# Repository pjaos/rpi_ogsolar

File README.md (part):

# OGSolar
An off grid Solar monitoring solution. This repo defines all the hardware 
(PCB and case design) and software needed. A diagram of the system is 
shown below.

The system is sited in a shed in my garden with two 200W solar panels 
mounted on the roof of the shed. The Epsolar Tracer 4120 MPPT controller
is connected to a 40AH LION battery.

The AC OUT feed is used to power a pond pump. This is powered from the
battery when sufficient charge is available and from an AC supply when
insufficient charge is available on the battery.

The DC out feed is used to power a charging station (phones/tablets etc)
inside my house. This cuts out when the voltage on the battery drops to a
low level.

The controller is a Raspberry Pi with a PCB (detailed bellow) connected 
that provides the ability to control power, measure voltage, current 
and temperatures and also extends a WiFi network into the (metal) shed.

## Controller Hardware Design.

The OGSolar controller consists of a Raspberry Pi with a header PCB.
This header PCB provides the ability to switch two loads using MOSFET
outputs and another two loads using relay outputs. It also provides the 
ability to monitor the voltage and current drawn along with the 
temperature of the Raspberry Pi processor and the heat sink 
temperature.

The LED on the PCB will light when the unit is connected to the WiFi network.

This project is an update of a previous off grid solar project that has been running for over 7 years. Details of this project can be found [here](https://projects.pausten.me.uk/ogsolar_project.html)

## Software Design.
The software architecture chosen uses a micro services pattern. I used this project
as a testing ground for a micro services architecture. I found that 

- The initial implementation cost was a bit higher than other approaches mostly due to the
requirement to manage data flow between the entities in the system.
- Fixing bugs/issues was easier as it was generally easier to determine the root cause of
performance issues due to the nature of distributed system responsibilities. 

The above architecture uses a Tornado web server. This presents a local web interface (shown below). 
The web interface uses bootstrap to allow the layout to resize itself. 
I used [bootstrap studio](https://bootstrapstudio.io/) to design the web interface as this 
reduced the effort required to design a maintain a web interface. 
The ogsolar/www folder contains a bootstrap studio project file for the design.

The software running on the Raspberry Pi also connects to the [Yview Framework](https://github.com/pjaos/yview)
which allows integration with servers running database systems and webservers. 
The OGSolar device works without connecting to the YView network but the YView
network provides access to a wider network of devices using technologies such 
as MQTT servers. An example of the OGsolar unit providing data to such a
system can be found [here](https://projects.pausten.me.uk/ogsolar_history.html).
This shows live data from a running OGSolar unit.

### Embedded Device Software
The OGSolar device is command line driven. When the ogsolar package is installed two programs are available 'ogsolar' and 'tracer'. ogsolar is the application that runs the system operation and tracer is a command line tool that allows direct connection to the EPSolar Tracer 4210 MPPT solar charger. 

#### OGSolar
The ogsolar application can be executed from the Linux command line and has help text as shown below.

```
ogsolar -h
Usage: An application to control an off grid solar installation. Specifically for use with an EPSolar Tracer MPPT controller connected to a battery (Lithium or Lead Acid). An inverter can be used to power devices when sufficient charge is available on the battery.

Options:
  -h, --help            show this help message and exit
  --config              Set the configuration parameters.
  --cal                 Calibrate the voltage and current measurements.
  --quiet               Do not display messages on stdout.
  --inv_on              On startup set the inverter on and select the inverter
                        output. By default the inverter is off and mains AC is
                        selected.
  --web_root=WEB_ROOT   The web root dir (default=/tmp/ogsolar_webroot).
  --max_mem_inc=MAX_MEM_INC
                        The maximum memory (RAM) increase of ogsolar
                        controller software before rebooting the system
                        (default = 10000 kB).
  --sim_json=SIM_JSON   Developer use only. Simulate tracer MPPT Ctrl
                        hardware. A JSON file is needed as the argument. This
                        is a file saved using menu option 2 when running the
                        tracer command. This saves a JSON file with the state
                        of all the tracer unit registers.
  --tracer_log=TRACER_LOG
                        Log file for EPSolar Tracer register values (default =
                        none). If --sim_tracer is used then tracer register
                        values are read from this file. If --sim_tracer is not
                        used then register values read from the Tracer
                        hardware are written (appended) to this file.
  --sim_ads1115         Developer use only. Simulate the ADS1115 ADC on I2c
                        bus hardware.
  --off                 Switch off inverter and spare relay.
  --debug               Enable debugging.
  --no_reboot           In the event of an error a reboot will occur to try
                        and recover. If this option is used this does not
                        occur.
  --enable_auto_start   Auto start when this computer starts.
  --user=USER           The user name when the --enable_auto_start argument is
                        used (default=auser)
  --disable_auto_start  Disable auto starting when this computer starts.
  --check_auto_start    Check the status of an auto started ogsolar instance.
  --dv                  Debug the voltage reading. Read and display the
                        voltage every second.
  --dc                  Debug the current reading. Read and display the
                        current (Amps) every second.
  --dht                 Debug the heatsink temperature reading. Read and
                        display the temperature every second.
  --dpt                 Debug the processor temperature reading. Read and
                        display the temperature every second.
  --tgpio               Toggle the GPIO lines for debugging purposes.
  --rsw                 Read the state of the switch for debugging purposes.
  --l1=L1               Set load 1 on/off (1/0) for debugging purposes. This
                        output should be connected to the inverter.
  --l2=L2               Set load 2 on/off (1/0) for debugging purposes.
  --invr=INVR           Set the inverter relay output on/off (1/0) for
                        debugging purposes.
  --sparer=SPARER       Set the spare relay output on/off (1/0) for debugging
                        purposes.
```

Once configured as detailed [here](docs/commissioning_the_raspberry_pi.md) the solar command can be executed from the command line (without arguments) and will produce output similar to that detailed below.

```
auser@raspberrypi:/tmp $ ogsolar
INFO:  Loaded config from /home/auser/.ogsolar.cfg
INFO:  STARTUP: ogsolar
INFO:  Starting web server.INFO:  Listening on UDP port 2934
INFO:  Turn spare relay OFF
INFO:  select AC source from Mains AC
INFO:  Set inverter output OFF.
INFO:  Set inverter output OFF.
INFO:  Loaded config from /home/auser/.ogsolar_adc_cal.cfg
INFO:  Set inverter off initial state.
INFO:  Set inverter output OFF.
INFO:  Turned load 1 OFF
INFO:  select AC source from Mains AC
INFO:  ------------------> Selected AC from mains supply.
INFO:  Set inverter output ON.
INFO:  Turned load 2 ON
INFO:  Heat sink: 22.3 °C
INFO:  CPU:       40.3 °C
INFO:  Load AMPS: 0.286, Load WATTS 4.263
INFO:  Battery charge state = Not Charging
INFO:  Load 1 OFF:  Battery volts: 14.600. Waiting for battery voltage to reach 15.950 volts.
INFO:  Load 2 ON:  Battery volts: 14.600. Waiting for battery voltage to drop to 14.400 volts.
INFO:  STARTUP: 9 threads running
INFO:  9 threads running (min=8).
INFO:  Memory in use = 18772 kB, increase since startup = 0 kB (max = 10000 kB).
INFO:  Seconds since last AYT reception: 5
INFO:  ipAddress=192.168.1.93
INFO:  Listening on UDP port 2934
INFO:  Turned LED ON
INFO:  9 threads running (min=8).
INFO:  Memory in use = 18772 kB, increase since startup = 0 kB (max = 10000 kB).
INFO:  Heat sink: 22.3 °C
INFO:  CPU:       40.2 °C
INFO:  Load AMPS: 0.262, Load WATTS 3.906
INFO:  Battery charge state = Not Charging
INFO:  Load 1 OFF:  Battery volts: 14.590. Waiting for battery voltage to reach 15.950 volts.
INFO:  Load 2 ON:  Battery volts: 14.590. Waiting for battery voltage to drop to 14.400 volts.
INFO:  9 threads running (min=8).
INFO:  Memory in use = 18936 kB, increase since startup = 164 kB (max = 10000 kB).
INFO:  ipAddress=192.168.1.93
INFO:  Heat sink: 22.3 °C
INFO:  CPU:       40.1 °C
INFO:  Load AMPS: 0.273, Load WATTS 4.067
INFO:  Battery charge state = Not Charging
INFO:  Load 1 OFF:  Battery volts: 14.590. Waiting for battery voltage to reach 15.950 volts.
INFO:  Load 2 ON:  Battery volts: 14.590. Waiting for battery voltage to drop to 14.400 volts.
INFO:  9 threads running (min=8).
INFO:  Memory in use = 18936 kB, increase since startup = 164 kB (max = 10000 kB).
INFO:  ipAddress=192.168.1.93
INFO:  9 threads running (min=8).
INFO:  Memory in use = 18936 kB, increase since startup = 164 kB (max = 10000 kB).
INFO:  Heat sink: 22.3 °C
INFO:  CPU:       40.1 °C
INFO:  Load AMPS: 0.268, Load WATTS 3.994
INFO:  Battery charge state = Not Charging
INFO:  Load 1 OFF:  Battery volts: 14.600. Waiting for battery voltage to reach 15.950 volts.
INFO:  Load 2 ON:  Battery volts: 14.600. Waiting for battery voltage to drop to 14.400 volts.
INFO:  9 threads running (min=8).
INFO:  Memory in use = 18936 kB, increase since startup = 164 kB (max = 10000 kB).
```

The application will monitor the battery voltage and turn on load 1 & 2 if above a minimum voltages. Separate on/off voltage levels can be configured for Load 1 and Load 2. Other information is also reported (E.G heatsink, CPU temperature and Tracer MPPT unit register values). The OGsolar device can be configured to generate syslog data which can be sent to an external syslog server (it is not recommended that the local RPi syslog server is ued to to excessive SD card writes). An example of this data from the syslog server is shown below.

```
pja@lmserver:~$ sudo tail -f /var/log/syslog | grep 192.168.1.98
Oct 19 05:00:27 192.168.1.98 14399 root: STARTUP: ogsolar
Oct 19 05:00:30 192.168.1.98 14439 auser: STARTUP: ogsolar
Oct 19 05:00:30 192.168.1.98 14439 auser: Listening on UDP port 2934
Oct 19 05:00:30 192.168.1.98 14439 auser: Starting web server.
Oct 19 05:00:30 192.168.1.98 14439 auser: Turn spare relay OFF
Oct 19 05:00:30 192.168.1.98 14439 auser: select AC source from Mains AC
Oct 19 05:00:30 192.168.1.98 14439 auser: Set inverter output OFF.
Oct 19 05:00:30 192.168.1.98 14439 auser: Set inverter output OFF.
Oct 19 05:00:30 192.168.1.98 14439 auser: CODES_PER_AMP = 1221
Oct 19 05:00:30 192.168.1.98 14439 auser: CODES_PER_VOLT = 1270
Oct 19 05:00:30 192.168.1.98 14439 auser: NO_CURRENT_CODES = 64
Oct 19 05:00:30 192.168.1.98 14439 auser: Loaded config from /home/auser/.ogsolar_adc_cal.cfg
Oct 19 05:00:30 192.168.1.98 14439 auser: Set inverter off initial state.
Oct 19 05:00:30 192.168.1.98 14439 auser: Set inverter output OFF.
Oct 19 05:00:30 192.168.1.98 14439 auser: Turned load 1 OFF
Oct 19 05:00:32 192.168.1.98 14439 auser: select AC source from Mains AC
Oct 19 05:00:32 192.168.1.98 14439 auser: ------------------> Selected AC from mains supply.
Oct 19 05:00:32 192.168.1.98 14439 auser: Set inverter output ON.
Oct 19 05:00:32 192.168.1.98 14439 auser: Turned load 2 ON
Oct 19 05:00:32 192.168.1.98 14439 auser: EPSolarTracerInterface:_processCmd: 1
Oct 19 05:00:33 192.168.1.98 14439 auser: >>>>>>>>>>>>>>>>>>>>>>>>>>>>> Min battery charge temp (C): 0.0
Oct 19 05:00:33 192.168.1.98 14439 auser: BATTERY CHARGE STATUS=Not Charging
Oct 19 05:00:33 192.168.1.98 14439 auser: PV VOLTS=0
Oct 19 05:00:33 192.168.1.98 14439 auser: PV AMPS=0
Oct 19 05:00:33 192.168.1.98 14439 auser: BATTERY VOLTS=14.59
Oct 19 05:00:33 192.168.1.98 14439 auser: BATTERY AMPS IN=0
Oct 19 05:00:33 192.168.1.98 14439 auser: PV WATTS=0
Oct 19 05:00:33 192.168.1.98 14439 auser: BATTERY WATTS IN=0
Oct 19 05:00:33 192.168.1.98 14439 auser: BATTERY TEMPERATURE (C)=14.59
Oct 19 05:00:33 192.168.1.98 14439 auser: CONTROLLER TEMPERATURE (C)=17.8
Oct 19 05:00:33 192.168.1.98 14439 auser: MPPT_LOAD_VOLTS=0
Oct 19 05:00:33 192.168.1.98 14439 auser: MPPT_LOAD_AMPS=0
Oct 19 05:00:33 192.168.1.98 14439 auser: MPPT_LOAD_WATTS=0
Oct 19 05:00:33 192.168.1.98 14439 auser: GENERATED KW=744.1
Oct 19 05:00:33 192.168.1.98 14439 auser: GENERATED KW TODAY=0
Oct 19 05:00:33 192.168.1.98 14439 auser: GENERATED KW THIS MONTH=8.02
Oct 19 05:00:33 192.168.1.98 14439 auser: GENERATED KW THIS YEAR=63.71
Oct 19 05:00:33 192.168.1.98 14439 auser: Heat sink: 22.3 C
Oct 19 05:00:33 192.168.1.98 14439 auser: CPU:       40.1 C
Oct 19 05:00:33 192.168.1.98 14439 auser: AMPS = 0.283
Oct 19 05:00:33 192.168.1.98 14439 auser: Load AMPS: 0.283, Load WATTS 4.225
Oct 19 05:00:33 192.168.1.98 14439 auser: Battery charge state = Not Charging
Oct 19 05:00:33 192.168.1.98 14439 auser: Load 1 OFF:  Battery volts: 14.590. Waiting for battery voltage to reach 15.950 volts.
Oct 19 05:00:33 192.168.1.98 14439 auser: Load 2 ON:  Battery volts: 14.590. Waiting for battery voltage to drop to 14.400 volts.
Oct 19 05:00:35 192.168.1.98 14439 auser: STARTUP: 9 threads running
Oct 19 05:00:35 192.168.1.98 14439 auser: 9 threads running (min=8).
Oct 19 05:00:35 192.168.1.98 14439 auser: Memory in use = 18496 kB, increase since startup = 0 kB (max = 10000 kB).
Oct 19 05:00:40 192.168.1.98 14439 auser: 9 threads running (min=8).
Oct 19 05:00:40 192.168.1.98 14439 auser: Memory in use = 18892 kB, increase since startup = 396 kB (max = 10000 kB).
Oct 19 05:00:40 192.168.1.98 14439 auser: EPSolarTracerInterface:_processCmd: 1
Oct 19 05:00:41 192.168.1.98 14439 auser: >>>>>>>>>>>>>>>>>>>>>>>>>>>>> Min battery charge temp (C): 0.0
Oct 19 05:00:41 192.168.1.98 14439 auser: BATTERY CHARGE STATUS=Not Charging
Oct 19 05:00:41 192.168.1.98 14439 auser: PV VOLTS=0.02
Oct 19 05:00:41 192.168.1.98 14439 auser: PV AMPS=0
Oct 19 05:00:41 192.168.1.98 14439 auser: BATTERY VOLTS=14.59
Oct 19 05:00:41 192.168.1.98 14439 auser: BATTERY AMPS IN=0
Oct 19 05:00:41 192.168.1.98 14439 auser: PV WATTS=0
Oct 19 05:00:41 192.168.1.98 14439 auser: BATTERY WATTS IN=0
Oct 19 05:00:41 192.168.1.98 14439 auser: BATTERY TEMPERATURE (C)=14.58
Oct 19 05:00:41 192.168.1.98 14439 auser: CONTROLLER TEMPERATURE (C)=17.8
Oct 19 05:00:41 192.168.1.98 14439 auser: MPPT_LOAD_VOLTS=0
Oct 19 05:00:41 192.168.1.98 14439 auser: MPPT_LOAD_AMPS=0
Oct 19 05:00:41 192.168.1.98 14439 auser: MPPT_LOAD_WATTS=0
Oct 19 05:00:41 192.168.1.98 14439 auser: GENERATED KW=744.1
Oct 19 05:00:41 192.168.1.98 14439 auser: GENERATED KW TODAY=0
Oct 19 05:00:41 192.168.1.98 14439 auser: GENERATED KW THIS MONTH=8.02
Oct 19 05:00:41 192.168.1.98 14439 auser: GENERATED KW THIS YEAR=63.71
Oct 19 05:00:41 192.168.1.98 14439 auser: Heat sink: 22.3 C
Oct 19 05:00:41 192.168.1.98 14439 auser: CPU:       40.0 C
Oct 19 05:00:41 192.168.1.98 14439 auser: AMPS = 0.274
Oct 19 05:00:41 192.168.1.98 14439 auser: Load AMPS: 0.274, Load WATTS 4.090
Oct 19 05:00:41 192.168.1.98 14439 auser: Battery charge state = Not Charging
Oct 19 05:00:41 192.168.1.98 14439 auser: Load 1 OFF:  Battery volts: 14.590. Waiting for battery voltage to reach 15.950 volts.
Oct 19 05:00:41 192.168.1.98 14439 auser: Load 2 ON:  Battery volts: 14.590. Waiting for battery voltage to drop to 14.400 volts.
Oct 19 05:00:42 192.168.1.98 14439 auser: Seconds since last AYT reception: 5
Oct 19 05:00:42 192.168.1.98 14439 auser: Listening on UDP port 2934
Oct 19 05:00:45 192.168.1.98 14439 auser: 9 threads running (min=8).
Oct 19 05:00:45 192.168.1.98 14439 auser: Memory in use = 18904 kB, increase since startup = 408 kB (max = 10000 kB).
Oct 19 05:00:46 192.168.1.98 14439 auser: ipAddress=192.168.1.98
Oct 19 05:00:46 192.168.1.98 14439 auser: Turned LED ON
```

#### Tracer
The tracer application can be executed from the Linux command line and has help text as shown below.

```
auser@raspberrypi:/tmp $ tracer -h
usage: tracer.py [-h] [-d] [-p PORT]

Responsible for access to read and write EPSolar Tracer registers.
via the modbus interface over the RS485 serial interface.
The Raspberry PI must have a USB RS485 adaptor connected to a USB port.

optional arguments:
  -h, --help            show this help message and exit
  -d, --debug           Enable debugging.
  -p PORT, --port PORT  The USB port (default=/dev/ttyUSB0).
```

When executed from the command line the tracer command shows a menu of options as shown below. The example below shows a read of all the Tracer devices registers over the modbus interface. The interface to the EPSolar tracer unit was written as part of the OGSolar application.

```
auser@raspberrypi:/tmp $ tracer
INFO:   1: Read all registers
INFO:   2: Save registers to JSON file.
INFO:   3: Load registers from a JSON file.
INFO:   4: Save registers to JSON file.
INFO:   5: Register read.
INFO:   6: Register write.
INFO:   7: Quit
INPUT: Select a menu option: 1
INFO:  Read all registers
INFO:  Took 0.6 seconds to read all registers.
INFO:  ----------------------------------------------------------
self._address          = 0x0002/2
self._regName          = Manual control the load
self._descriptionLines = ('When the load is manual mode，1-manual on 0 -manual off',)
self._unit             = UNDEFINED
self._multiplier       = 1
self._access           = C_R/W
self._rawRegValue      = 0
self._value            = 0
self._lswRegName       = None
INFO:  ----------------------------------------------------------
self._address          = 0x0005/5
self._regName          = Enable load test mode
self._descriptionLines = ('1 Enable', '0 Disable(normal)')
self._unit             = UNDEFINED
self._multiplier       = 1
self._access           = C_R/W
self._rawRegValue      = 0
self._value            = 0
self._lswRegName       = None
INFO:  ----------------------------------------------------------
self._address          = 0x0006/6
self._regName          = Force the load on/off
self._descriptionLines = ('1 Turn on', '0 Turn off (used for temporary test of the load)')
self._unit             = UNDEFINED
self._multiplier       = 1
self._access           = C_R/W
self._rawRegValue      = 0
self._value            = 0
self._lswRegName       = None
INFO:  ----------------------------------------------------------
self._address          = 0x2000/8192
self._regName          = Over temperature inside the device
self._descriptionLines = ('1 The temperature inside the controller is higher than the over-temperature protection point.', '0 Normal')
self._unit             = UNDEFINED
self._multiplier       = 1
self._access           = D_R
self._rawRegValue      = 0
self._value            = 0
self._lswRegName       = None
INFO:  ----------------------------------------------------------
self._address          = 0x200c/8204
self._regName          = Day/Night
self._descriptionLines = ('1-Night, 0-Day',)
self._unit             = UNDEFINED
self._multiplier       = 1
self._access           = D_R
self._rawRegValue      = 1
self._value            = 1.0
self._lswRegName       = None
INFO:  ----------------------------------------------------------
self._address          = 0x3000/12288
self._regName          = Charging equipment rated input voltage
self._descriptionLines = ('PV array rated voltage',)
self._unit             = V
self._multiplier       = 100
self._access           = R
self._rawRegValue      = 10000
self._value            = 100.0
self._lswRegName       = None
INFO:  ----------------------------------------------------------
self._address          = 0x3001/12289
self._regName          = Charging equipment rated input current
self._descriptionLines = ('PV array rated current',)
self._unit             = A
self._multiplier       = 100
self._access           = R
self._rawRegValue      = 4000
self._value            = 40.0
self._lswRegName       = None
INFO:  ----------------------------------------------------------
self._address          = 0x3002/12290
self._regName          = Charging equipment rated input power L
self._descriptionLines = ('PV array rated power (low 16 bits)',)
self._unit             = W
self._multiplier       = 100
self._access           = R
self._rawRegValue      = 38464
self._value            = 384.64
self._lswRegName       = None
INFO:  ----------------------------------------------------------
self._address          = 0x3003/12291
self._regName          = Charging equipment rated input power H
self._descriptionLines = ('PV array rated power (high 16 bits)',)
self._unit             = W
self._multiplier       = 100
self._access           = R
self._rawRegValue      = 1
self._value            = 1040.0
self._lswRegName       = Charging equipment rated input power L
INFO:  ----------------------------------------------------------
self._address          = 0x3004/12292
self._regName          = Charging equipment rated output voltage
self._descriptionLines = ("Battery's voltage",)
self._unit             = V
self._multiplier       = 100
self._access           = R
self._rawRegValue      = 2400
self._value            = 24.0
self._lswRegName       = None
INFO:  ----------------------------------------------------------
self._address          = 0x3005/12293
self._regName          = Charging equipment rated output current
self._descriptionLines = ('Rated charging current to battery',)
self._unit             = A
self._multiplier       = 100
self._access           = R
self._rawRegValue      = 4000
self._value            = 40.0
self._lswRegName       = None
INFO:  ----------------------------------------------------------
self._address          = 0x3006/12294
self._regName          = Charging equipment rated output power L
self._descriptionLines = ('Rated charging power to battery (low 16 bits)',)
self._unit             = W
self._multiplier       = 100
self._access           = R
self._rawRegValue      = 38464
self._value            = 384.64
self._lswRegName       = None
INFO:  ----------------------------------------------------------
self._address          = 0x3007/12295
self._regName          = Charging equipment rated output power H
self._descriptionLines = ('Rated charging power to battery (high 16 bits)',)
self._unit             = W
self._multiplier       = 100
self._access           = R
self._rawRegValue      = 1
self._value            = 1040.0
self._lswRegName       = Charging equipment rated output power L
INFO:  ----------------------------------------------------------
self._address          = 0x3008/12296
self._regName          = Charging mode
self._descriptionLines = ('0001H-PWM',)
self._unit             = UNDEFINED
self._multiplier       = 1
self._access           = R
self._rawRegValue      = 2
self._value            = 2.0
self._lswRegName       = None
INFO:  ----------------------------------------------------------
self._address          = 0x300e/12302
self._regName          = Rated output current of load
self._descriptionLines = ('',)
self._unit             = A
self._multiplier       = 100
self._access           = R
self._rawRegValue      = 4000
self._value            = 40.0
self._lswRegName       = None
INFO:  ----------------------------------------------------------
self._address          = 0x3100/12544
self._regName          = Charging equipment input voltage
self._descriptionLines = Solar charge controller--PV array voltage
self._unit             = V
self._multiplier       = 100
self._access           = R
self._rawRegValue      = 0
self._value            = 0
self._lswRegName       = None
INFO:  ----------------------------------------------------------
self._address          = 0x3101/12545
self._regName          = Charging equipment input current
self._descriptionLines = Solar charge controller--PV array current
self._unit             = A
self._multiplier       = 100
self._access           = R
self._rawRegValue      = 0
self._value            = 0
self._lswRegName       = None
INFO:  ----------------------------------------------------------
self._address          = 0x3102/12546
self._regName          = Charging equipment input power L
self._descriptionLines = ('Solar charge controller--PV array power (low 16 bits)',)
self._unit             = W
self._multiplier       = 100
self._access           = R
self._rawRegValue      = 0
self._value            = 0
self._lswRegName       = None
INFO:  ----------------------------------------------------------
self._address          = 0x3103/12547
self._regName          = Charging equipment input power H
self._descriptionLines = ('Solar charge controller--PV array power (high 16 bits)',)
self._unit             = W
self._multiplier       = 100
self._access           = R
self._rawRegValue      = 0
self._value            = 0
self._lswRegName       = Charging equipment input power L
INFO:  ----------------------------------------------------------
self._address          = 0x3104/12548
self._regName          = Charging equipment output voltage
self._descriptionLines = ('Battery voltage',)
self._unit             = V
self._multiplier       = 100
self._access           = R
self._rawRegValue      = 1461
self._value            = 14.61
self._lswRegName       = None
INFO:  ----------------------------------------------------------
self._address          = 0x3105/12549
self._regName          = Charging equipment output current
self._descriptionLines = ('Battery charging current',)
self._unit             = A
self._multiplier       = 100
self._access           = R
self._rawRegValue      = 0
self._value            = 0
self._lswRegName       = None
INFO:  ----------------------------------------------------------
self._address          = 0x3106/12550
self._regName          = Charging equipment output power L
self._descriptionLines = Battery charging power (low 16 bits)
self._unit             = W
self._multiplier       = 100
self._access           = R
self._rawRegValue      = 0
self._value            = 0
self._lswRegName       = None
INFO:  ----------------------------------------------------------
self._address          = 0x3107/12551
self._regName          = Charging equipment output power H
self._descriptionLines = ('Battery charging power (high 16 bits)',)
self._unit             = W
self._multiplier       = 100
self._access           = R
self._rawRegValue      = 0
self._value            = 0
self._lswRegName       = Charging equipment output power L
INFO:  ----------------------------------------------------------
self._address          = 0x310c/12556
self._regName          = Discharging equipment output voltage
self._descriptionLines = ('Load voltage',)
self._unit             = V
self._multiplier       = 100
self._access           = R
self._rawRegValue      = 0
self._value            = 0
self._lswRegName       = None
INFO:  ----------------------------------------------------------
self._address          = 0x310d/12557
self._regName          = Discharging equipment output current
self._descriptionLines = ('Load current',)
self._unit             = A
self._multiplier       = 100
self._access           = R
self._rawRegValue      = 0
self._value            = 0
self._lswRegName       = None
INFO:  ----------------------------------------------------------
self._address          = 0x310e/12558
self._regName          = Discharging equipment output power L
self._descriptionLines = ('Load power (low 16 bits)',)
self._unit             = W
self._multiplier       = 100
self._access           = R
self._rawRegValue      = 0
self._value            = 0
self._lswRegName       = None
INFO:  ----------------------------------------------------------
self._address          = 0x310f/12559
self._regName          = Discharging equipment output power H
self._descriptionLines = ('Load power (high 16 bits)',)
self._unit             = W
self._multiplier       = 100
self._access           = R
self._rawRegValue      = 0
self._value            = 0
self._lswRegName       = Discharging equipment output power L
INFO:  ----------------------------------------------------------
self._address          = 0x3110/12560
self._regName          = Battery Temperature
self._descriptionLines = ('Battery Temperature',)
self._unit             = C
self._multiplier       = 100
self._access           = R
self._rawRegValue      = 1456
self._value            = 14.56
self._lswRegName       = None
INFO:  ----------------------------------------------------------
self._address          = 0x3111/12561
self._regName          = Temperature inside equipment
self._descriptionLines = ('Temperature inside case',)
self._unit             = C
self._multiplier       = 100
self._access           = R
self._rawRegValue      = 1780
self._value            = 17.8
self._lswRegName       = None
INFO:  ----------------------------------------------------------
self._address          = 0x3112/12562
self._regName          = Power components temperature
self._descriptionLines = ('Heat sink surface temperature of equipments power components',)
self._unit             = C
self._multiplier       = 100
self._access           = R
self._rawRegValue      = 1780
self._value            = 17.8
self._lswRegName       = None
INFO:  ----------------------------------------------------------
self._address          = 0x311a/12570
self._regName          = Battery SOC
self._descriptionLines = ("The percentage of battery's remaining capacity",)
self._unit             = UNDEFINED
self._multiplier       = 100
self._access           = R
self._rawRegValue      = 63
self._value            = 0.63
self._lswRegName       = None
INFO:  ----------------------------------------------------------
self._address          = 0x311b/12571
self._regName          = Remote battery temperature
self._descriptionLines = ('The battery tempeture measured by remote temperature sensor',)
self._unit             = C
self._multiplier       = 100
self._access           = R
self._rawRegValue      = 1456
self._value            = 14.56
self._lswRegName       = None
INFO:  ----------------------------------------------------------
self._address          = 0x311d/12573
self._regName          = Battery's real rated power
self._descriptionLines = ('Current system rated votlage. 1200, 2400 represent 12V, 24V',)
self._unit             = V
self._multiplier       = 100
self._access           = R
self._rawRegValue      = 1200
self._value            = 12.0
self._lswRegName       = None
INFO:  ----------------------------------------------------------
self._address          = 0x3200/12800
self._regName          = Battery status
self._descriptionLines = ('D3-D0: 01H Overvolt , 00H Normal , 02H Under', 'Volt, 03H Low Volt Disconnect, 04H Fault', 'D7-D4: 00H Normal, 01H Over Temp.(Higher', 'than the warning settings), 02H Low Temp.(', 'Lower than the warning settings),', 'D8: Battery inerternal resistance abnormal 1,', 'normal 0', 'D15: 1-Wrong identification for rated voltage')
self._unit             = UNDEFINED
self._multiplier       = 1
self._access           = R
self._rawRegValue      = 3
self._value            = 3.0
self._lswRegName       = None
INFO:  ----------------------------------------------------------
self._address          = 0x3201/12801
self._regName          = Charging equipment status
self._descriptionLines = ('D15-D14: Input volt status. 00 normal, 01 no', 'power connected, 02H Higher volt input, 03H', 'Input volt error.', 'D13: Charging MOSFET is short.', 'D12: Charging or Anti-reverse MOSFET is short.', 'D11: Anti-reverse MOSFET is short.', 'D10: Input is over current.', 'D9: The load is Over current.', 'D8: The load is short.', 'D7: Load MOSFET is short.', 'D4: PV Input is short.', 'D3-2: Charging status. 00 No charging,01 Float,02', 'Boost,03 Equlization.', 'D1: 0 Normal, 1 Fault.', 'D0: 1 Running, 0 Standby.')
self._unit             = UNDEFINED
self._multiplier       = 1
self._access           = R
self._rawRegValue      = 1
self._value            = 1.0
self._lswRegName       = None
INFO:  ----------------------------------------------------------
self._address          = 0x3300/13056
self._regName          = Maximum input volt (PV) today
self._descriptionLines = ('00: 00 Refresh every day',)
self._unit             = V
self._multiplier       = 100
self._access           = R
self._rawRegValue      = 8
self._value            = 0.08
self._lswRegName       = None
INFO:  ----------------------------------------------------------
self._address          = 0x3301/13057
self._regName          = Minimum input volt (PV) today
self._descriptionLines = ('00: 00 Refresh every day',)
self._unit             = V
self._multiplier       = 100
self._access           = R
self._rawRegValue      = 0
self._value            = 0
self._lswRegName       = None
INFO:  ----------------------------------------------------------
self._address          = 0x3302/13058
self._regName          = Maximum battery volt today
self._descriptionLines = ('00: 00 Refresh every day',)
self._unit             = V
self._multiplier       = 100
self._access           = R
self._rawRegValue      = 1465
self._value            = 14.65
self._lswRegName       = None
INFO:  ----------------------------------------------------------
self._address          = 0x3303/13059
self._regName          = Minimum battery volt today
self._descriptionLines = ('00: 00 Refresh every day',)
self._unit             = V
self._multiplier       = 100
self._access           = R
self._rawRegValue      = 1454
self._value            = 14.54
self._lswRegName       = None
INFO:  ----------------------------------------------------------
self._address          = 0x3304/13060
self._regName          = Consumed energy today L
self._descriptionLines = ('00: 00 Clear every day (low 16 bits ',)
self._unit             = KWH
self._multiplier       = 100
self._access           = R
self._rawRegValue      = 0
self._value            = 0
self._lswRegName       = None
INFO:  ----------------------------------------------------------
self._address          = 0x3305/13061
self._regName          = Consumed energy today H
self._descriptionLines = ('00: 00 Clear every day (high 16 bits)',)
self._unit             = KWH
self._multiplier       = 100
self._access           = R
self._rawRegValue      = 0
self._value            = 0
self._lswRegName       = Consumed energy today L
INFO:  ----------------------------------------------------------
self._address          = 0x3306/13062
self._regName          = Consumed energy this month L
self._descriptionLines = ('00: 00 Clear on the first day of month (low 16 bits)',)
self._unit             = KWH
self._multiplier       = 100
self._access           = R
self._rawRegValue      = 17
self._value            = 0.17
self._lswRegName       = None
INFO:  ----------------------------------------------------------
self._address          = 0x3307/13063
self._regName          = Consumed energy this month H
self._descriptionLines = ('00: 00 Clear on the first day of month (high 16 bits)',)
self._unit             = KWH
self._multiplier       = 100
self._access           = R
self._rawRegValue      = 0
self._value            = 0.17
self._lswRegName       = Consumed energy this month L
INFO:  ----------------------------------------------------------
self._address          = 0x3308/13064
self._regName          = Consumed energy this year L
self._descriptionLines = ('00: 00 Clear on 1, Jan (low 16 bits)',)
self._unit             = KWH
self._multiplier       = 100
self._access           = R
self._rawRegValue      = 116
self._value            = 1.16
self._lswRegName       = None
INFO:  ----------------------------------------------------------
self._address          = 0x3309/13065
self._regName          = Consumed energy this year H
self._descriptionLines = ('00: 00 Clear on 1, Jan (high 16 bits)',)
self._unit             = KWH
self._multiplier       = 100
self._access           = R
self._rawRegValue      = 0
self._value            = 1.16
self._lswRegName       = Consumed energy this year L
INFO:  ----------------------------------------------------------
self._address          = 0x330a/13066
self._regName          = Total consumed energy L
self._descriptionLines = ('(low 16 bits)',)
self._unit             = KWH
self._multiplier       = 100
self._access           = R
self._rawRegValue      = 203
self._value            = 133038.08
self._lswRegName       = Total consumed energy H
INFO:  ----------------------------------------------------------
self._address          = 0x330b/13067
self._regName          = Total consumed energy H
self._descriptionLines = ('(high 16 bits)',)
self._unit             = KWH
self._multiplier       = 100
self._access           = R
self._rawRegValue      = 0
self._value            = 0
self._lswRegName       = None
INFO:  ----------------------------------------------------------
self._address          = 0x330c/13068
self._regName          = Generated energy today L
self._descriptionLines = ('00: 00 Clear every day (low 16 bits)',)
self._unit             = KWH
self._multiplier       = 100
self._access           = R
self._rawRegValue      = 0
self._value            = 0
self._lswRegName       = None
INFO:  ----------------------------------------------------------
self._address          = 0x330d/13069
self._regName          = Generated energy today H
self._descriptionLines = ('(high 16 bits)',)
self._unit             = KWH
self._multiplier       = 100
self._access           = R
self._rawRegValue      = 0
self._value            = 0
self._lswRegName       = Generated energy today L
INFO:  ----------------------------------------------------------
self._address          = 0x330e/13070
self._regName          = Generated energy this month L
self._descriptionLines = ('00: 00 Clear on the first day of month (low 16 bits)',)
self._unit             = KWH
self._multiplier       = 100
self._access           = R
self._rawRegValue      = 802
self._value            = 8.02
self._lswRegName       = None
INFO:  ----------------------------------------------------------
self._address          = 0x330f/13071
self._regName          = Generated energy this month H
self._descriptionLines = ('(high 16 bits)',)
self._unit             = KWH
self._multiplier       = 100
self._access           = R
self._rawRegValue      = 0
self._value            = 8.02
self._lswRegName       = Generated energy this month L
INFO:  ----------------------------------------------------------
self._address          = 0x3310/13072
self._regName          = Generated energy this year L
self._descriptionLines = ('00: 00 Clear on 1, Jan (low 16 bits)',)
self._unit             = KWH
self._multiplier       = 100
self._access           = R
self._rawRegValue      = 6371
self._value            = 63.71
self._lswRegName       = None
INFO:  ----------------------------------------------------------
self._address          = 0x3311/13073
self._regName          = Generated energy this year H
self._descriptionLines = ('(high 16 bits)',)
self._unit             = KWH
self._multiplier       = 100
self._access           = R
self._rawRegValue      = 0
self._value            = 63.71
self._lswRegName       = Generated energy this year L
INFO:  ----------------------------------------------------------
self._address          = 0x3312/13074
self._regName          = Total generated energy L
self._descriptionLines = ('(low 16 bits)',)
self._unit             = KWH
self._multiplier       = 100
self._access           = R
self._rawRegValue      = 8874
self._value            = 88.74
self._lswRegName       = None
INFO:  ----------------------------------------------------------
self._address          = 0x3313/13075
self._regName          = Total generated energy H
self._descriptionLines = ('(high 16 bits)',)
self._unit             = KWH
self._multiplier       = 100
self._access           = R
self._rawRegValue      = 1
self._value            = 744.1
self._lswRegName       = Total generated energy L
INFO:  ----------------------------------------------------------
self._address          = 0x3314/13076
self._regName          = Carbon dioxide reduction L
self._descriptionLines = ('Saving 1 Kilowatt=Reduction 0.997KG (Carbon dioxide) = Reduction 0.272KG (Carton) (low 16 bits)',)
self._unit             = TON
self._multiplier       = 100
self._access           = R
self._rawRegValue      = 74
self._value            = 0.74
self._lswRegName       = None
INFO:  ----------------------------------------------------------
self._address          = 0x3315/13077
self._regName          = Carbon dioxide reduction H
self._descriptionLines = ('(high 16 bits)',)
self._unit             = TON
self._multiplier       = 100
self._access           = R
self._rawRegValue      = 0
self._value            = 0.74
self._lswRegName       = Carbon dioxide reduction L
INFO:  ----------------------------------------------------------
self._address          = 0x331b/13083
self._regName          = Battery Current L
self._descriptionLines = ('The net battery current,charging current minus the discharging one.', 'The positive value represents A charging and negative, discharging (low 16 bits).')
self._unit             = A
self._multiplier       = 100
self._access           = R
self._rawRegValue      = 0
self._value            = 0
self._lswRegName       = None
INFO:  ----------------------------------------------------------
self._address          = 0x331c/13084
self._regName          = Battery Current H
self._descriptionLines = ('(high 16 bits)',)
self._unit             = A
self._multiplier       = 100
self._access           = R
self._rawRegValue      = 0
self._value            = 0
self._lswRegName       = Battery Current L
INFO:  ----------------------------------------------------------
self._address          = 0x331d/13085
self._regName          = Battery Temp
self._descriptionLines = ('Battery Temp.',)
self._unit             = C
self._multiplier       = 100
self._access           = R
self._rawRegValue      = 1456
self._value            = 14.56
self._lswRegName       = None
INFO:  ----------------------------------------------------------
self._address          = 0x331e/13086
self._regName          = Ambient Temp
self._descriptionLines = ('Ambient Temp.',)
self._unit             = C
self._multiplier       = 100
self._access           = R
self._rawRegValue      = 1456
self._value            = 14.56
self._lswRegName       = None
INFO:  ----------------------------------------------------------
self._address          = 0x9000/36864
self._regName          = Battery Type
self._descriptionLines = ('0001H- Sealed', '0002H- GEL', '0003H- Flooded', '0000H- User defined')
self._unit             = UNDEFINED
self._multiplier       = 1
self._access           = R/W
self._rawRegValue      = 0
self._value            = 0
self._lswRegName       = None
INFO:  ----------------------------------------------------------
self._address          = 0x9001/36865
self._regName          = Battery Capacity
self._descriptionLines = ('Rated capacity of the battery. PJA: The pdf does not state the multiplier for this, 1 is a guess.',)
self._unit             = AH
self._multiplier       = 1
self._access           = R/W
self._rawRegValue      = 200
self._value            = 200.0
self._lswRegName       = None
INFO:  ----------------------------------------------------------
self._address          = 0x9002/36866
self._regName          = Temperature compensation coefficient
self._descriptionLines = ('Range 0-9. PJA: -3 is the default value when read from the unit. This does not tie up with the range 0-9 stated in the pdf.',)
self._unit             = MV_C_2V
self._multiplier       = 100
self._access           = R/W
self._rawRegValue      = 300
self._value            = 3.0
self._lswRegName       = None
INFO:  ----------------------------------------------------------
self._address          = 0x9003/36867
self._regName          = High Volt.disconnect
self._descriptionLines = ('',)
self._unit             = V
self._multiplier       = 100
self._access           = R/W
self._rawRegValue      = 1637
self._value            = 16.37
self._lswRegName       = None
INFO:  ----------------------------------------------------------
self._address          = 0x9004/36868
self._regName          = Charging limit voltage
self._descriptionLines = ('',)
self._unit             = V
self._multiplier       = 100
self._access           = R/W
self._rawRegValue      = 1600
self._value            = 16.0
self._lswRegName       = None
INFO:  ----------------------------------------------------------
self._address          = 0x9005/36869
self._regName          = Over voltage reconnect
self._descriptionLines = ('',)
self._unit             = V
self._multiplier       = 100
self._access           = R/W
self._rawRegValue      = 1612
self._value            = 16.12
self._lswRegName       = None
INFO:  ----------------------------------------------------------
self._address          = 0x9006/36870
self._regName          = Equalization voltage
self._descriptionLines = ('',)
self._unit             = V
self._multiplier       = 100
self._access           = R/W
self._rawRegValue      = 1587
self._value            = 15.87
self._lswRegName       = None
INFO:  ----------------------------------------------------------
self._address          = 0x9007/36871
self._regName          = Boost voltage
self._descriptionLines = ('',)
self._unit             = V
self._multiplier       = 100
self._access           = R/W
self._rawRegValue      = 1587
self._value            = 15.87
self._lswRegName       = None
INFO:  ----------------------------------------------------------
self._address          = 0x9008/36872
self._regName          = Float voltage
self._descriptionLines = ('',)
self._unit             = V
self._multiplier       = 100
self._access           = R/W
self._rawRegValue      = 1584
self._value            = 15.84
self._lswRegName       = None
INFO:  ----------------------------------------------------------
self._address          = 0x9009/36873
self._regName          = Boost reconnect voltage
self._descriptionLines = ('',)
self._unit             = V
self._multiplier       = 100
self._access           = R/W
self._rawRegValue      = 1568
self._value            = 15.68
self._lswRegName       = None
INFO:  ----------------------------------------------------------
self._address          = 0x900a/36874
self._regName          = Low voltage reconnect
self._descriptionLines = ('',)
self._unit             = V
self._multiplier       = 100
self._access           = R/W
self._rawRegValue      = 1553
self._value            = 15.53
self._lswRegName       = None
INFO:  ----------------------------------------------------------
self._address          = 0x900b/36875
self._regName          = Under voltage recover
self._descriptionLines = ('',)
self._unit             = V
self._multiplier       = 100
self._access           = R/W
self._rawRegValue      = 1584
self._value            = 15.84
self._lswRegName       = None
INFO:  ----------------------------------------------------------
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
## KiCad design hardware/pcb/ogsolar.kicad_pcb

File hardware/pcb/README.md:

These are Kicad 5.1 project files.

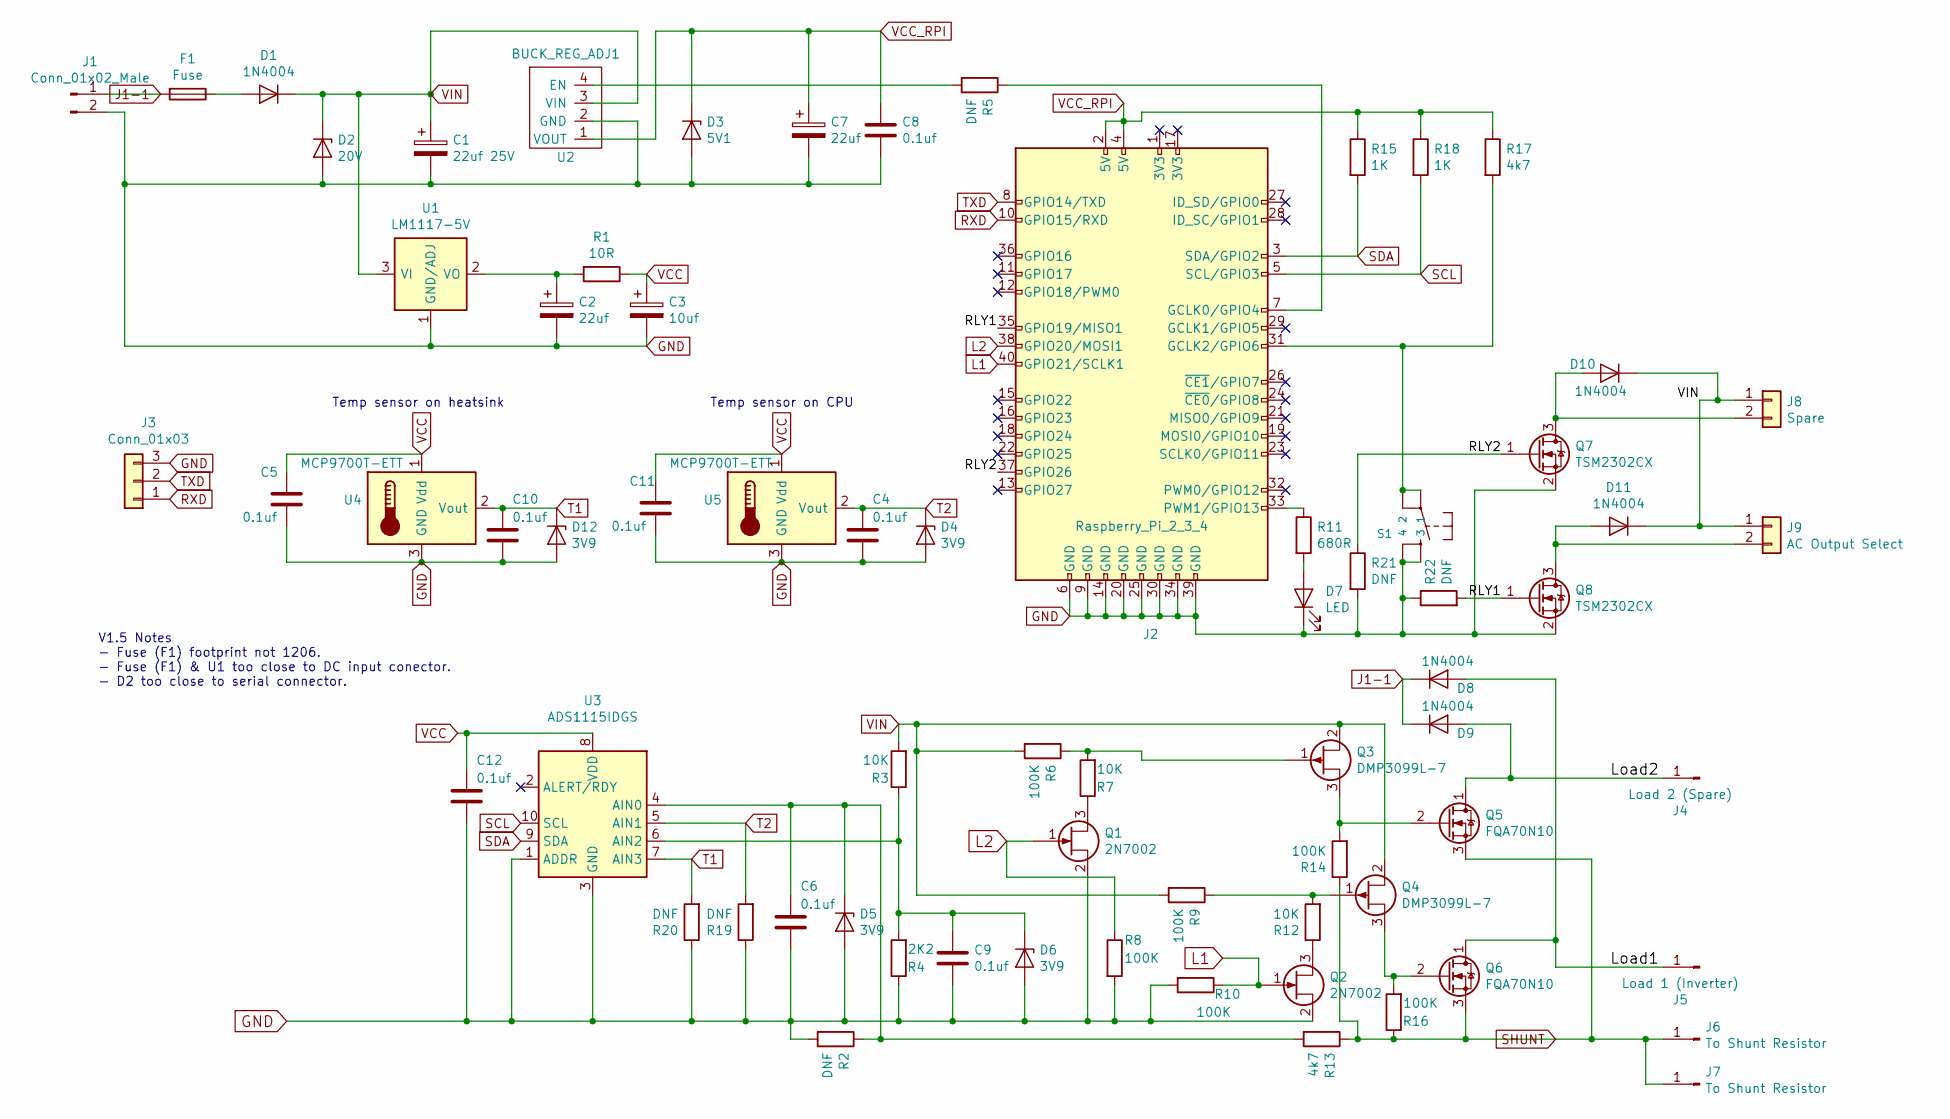
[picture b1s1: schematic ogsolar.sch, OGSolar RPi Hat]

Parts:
C1: 22uf 25V; CP_EIA-6032-15_Kemet-U_Pad2.25x2.35mm_HandSolder
C2, C7: 22uf; CP_EIA-6032-15_Kemet-U_Pad2.25x2.35mm_HandSolder
C3: 10uf; C_1210_3225Metric_Pad1.33x2.70mm_HandSolder
C4, C5, C6, C9, C10, C11, C12: 0.1uf; C_0603_1608Metric_Pad1.08x0.95mm_HandSolder
C8: 0.1uf; C_0504_1310Metric_Pad0.83x1.28mm_HandSolder
D1, D8, D9, D10, D11: 1N4004; D_MELF
D2: 20V; D_MicroMELF_Handsoldering
D3: 5V1; D_MicroMELF_Handsoldering
D4, D5, D6, D12: 3V9; D_MicroMELF_Handsoldering
D7: LED; LED_1206_3216Metric_Pad1.42x1.75mm_HandSolder
F1: Fuse; Fuse_2512_6332Metric_Pad1.52x3.35mm_HandSolder
J1: Conn_01x02_Male; JST_EH_B2B-EH-A_1x02_P2.50mm_Vertical
J2: Raspberry_Pi_2_3_4; PinHeader_2x20_P2.54mm_Vertical
J3: Conn_01x03; JST_EH_B3B-EH-A_1x03_P2.50mm_Vertical
J4: Load 2 (Spare); MountingHole_3.2mm_M3_Pad_Via
J5: Load 1 (Inverter); MountingHole_3.2mm_M3_Pad_Via
J6, J7: To Shunt Resistor; MountingHole_3.2mm_M3_Pad_Via
J8: Spare; JST_EH_B2B-EH-A_1x02_P2.50mm_Vertical
J9: AC Output Select; JST_EH_B2B-EH-A_1x02_P2.50mm_Vertical
Q1, Q2: 2N7002; SOT-23
Q3, Q4: DMP3099L-7; SOT-23
Q5, Q6: FQA70N10; TO-3PN__Vertical
Q7, Q8: TSM2302CX; SOT-23
R1: 10R; R_0603_1608Metric_Pad0.98x0.95mm_HandSolder
R2, R5, R19, R20, R21, R22: DNF; R_0603_1608Metric_Pad0.98x0.95mm_HandSolder
R3, R7, R12: 10K; R_0603_1608Metric_Pad0.98x0.95mm_HandSolder
R4: 2K2; R_0603_1608Metric_Pad0.98x0.95mm_HandSolder
R6, R8, R9, R10, R14, R16: 100K; R_0603_1608Metric_Pad0.98x0.95mm_HandSolder
R11: 680R; R_0603_1608Metric_Pad0.98x0.95mm_HandSolder
R13, R17: 4k7; R_0603_1608Metric_Pad0.98x0.95mm_HandSolder
R15, R18: 1K; R_0603_1608Metric_Pad0.98x0.95mm_HandSolder
S1: DTS-6; switch-tact-DTS-6
U1: LM1117-5V; SOT-223
U2: BUCK_REG_ADJ1; BUCK_REG_ADJ1_HORIZONTAL
U3: ADS1115IDGS; VSSOP-10_3x3mm_P0.5mm
U4, U5: MCP9700T-ETT; TO-92

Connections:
/Load1: D8.2 (A), J5.1, Q6.1 (D)
/Load2: D9.2 (A), J4.1, Q5.1 (D)
/RLY1: J2.35 (GPIO19/MISO1), Q8.1 (G), R22.2
/RLY2: J2.37 (GPIO26), Q7.1 (G), R21.1
GND: C1.2, C2.2, C3.2, C4.2, C5.2, C6.2, C7.2, C8.2, C9.2, C10.2, C11.2, C12.2, D2.2 (A), D3.2 (A), D4.2 (A), D5.2 (A), D6.2 (A), D7.1 (K), D12.2 (A), J1.2, J2.6 (GND), J2.9 (GND), J2.14 (GND), J2.20 (GND), J2.25 (GND), J2.30 (GND), J2.34 (GND), J2.39 (GND), J3.3, Q1.2 (S), Q2.2 (S), Q7.2 (S), Q8.2 (S), R2.2, R4.1, R8.2, R10.2, R19.1, R20.1, R21.2, R22.1, S1.3, S1.4, U1.1 (GND/ADJ), U2.2 (GND), U3.1 (ADDR), U3.3 (GND), U4.3 (GND), U5.3 (GND)
J1-1: D8.1 (K), D9.1 (K), F1.2, J1.1
L1: J2.40 (GPIO21/SCLK1), Q2.1 (G), R10.1
L2: J2.38 (GPIO20/MOSI1), Q1.1 (G), R8.1
unnamed: C2.1, R1.2, U1.2 (VO)
unnamed: C6.1, D5.1 (K), R2.1, R13.2, U3.4 (AIN0)
unnamed: C9.1, D6.1 (K), R3.1, R4.2, U3.6 (AIN2)
unnamed: D1.2 (A), F1.1
unnamed: D7.2 (A), R11.2
unnamed: D10.2 (A), J8.2, Q7.3 (D)
unnamed: D11.2 (A), J9.2, Q8.3 (D)
unnamed: J2.7 (GCLK0/GPIO4), R5.1
unnamed: J2.31 (GCLK2/GPIO6), R17.2, S1.1, S1.2
unnamed: J2.33 (PWM1/GPIO13), R11.1
unnamed: Q1.3 (D), R7.1
unnamed: Q2.3 (D), R12.1
unnamed: Q3.1 (G), R6.1, R7.2
unnamed: Q3.3 (S), Q5.2 (G), R14.2
unnamed: Q4.1 (G), R9.1, R12.2
unnamed: Q4.3 (S), Q6.2 (G), R16.2
unnamed: R5.2, U2.4 (EN)
RXD: J2.10 (GPIO15/RXD), J3.1
SCL: J2.5 (SCL/GPIO3), R18.2, U3.10 (SCL)
SDA: J2.3 (SDA/GPIO2), R15.2, U3.9 (SDA)
SHUNT: J6.1, J7.1, Q5.3 (S), Q6.3 (S), R13.1, R14.1, R16.1
T1: C10.1, D12.1 (K), R20.2, U3.7 (AIN3), U4.2 (Vout)
T2: C4.1, D4.1 (K), R19.2, U3.5 (AIN1), U5.2 (Vout)
TXD: J2.8 (GPIO14/TXD), J3.2
VCC: C3.1, C5.1, C11.1, C12.1, R1.1, U3.8 (VDD), U4.1 (Vdd), U5.1 (Vdd)
VCC_RPI: C7.1, C8.1, D3.1 (K), J2.2 (5V), J2.4 (5V), R15.1, R17.1, R18.1, U2.1 (VOUT)
VIN: C1.1, D1.1 (K), D2.1 (K), D10.1 (K), D11.1 (K), J8.1, J9.1, Q3.2 (D), Q4.2 (D), R3.2, R6.2, R9.2, U1.3 (VI), U2.3 (VIN)

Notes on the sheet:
Temp sensor on heatsink
Temp sensor on CPU
V1.5 Notes - Fuse (F1) footprint not 1206. - Fuse (F1) & U1 too close to DC input conector. - D2 too close to serial connector.

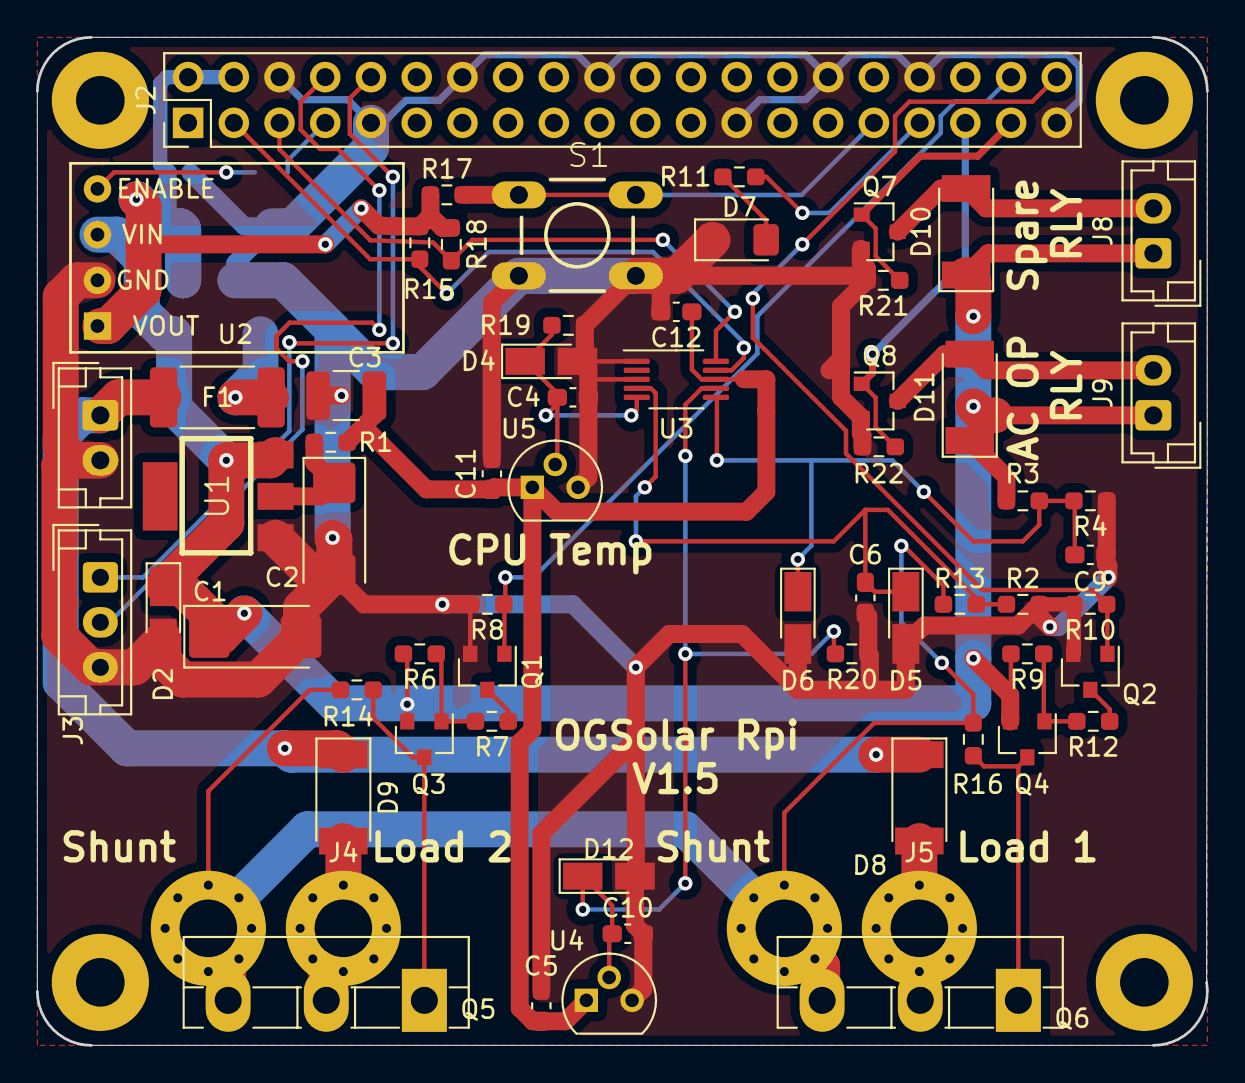
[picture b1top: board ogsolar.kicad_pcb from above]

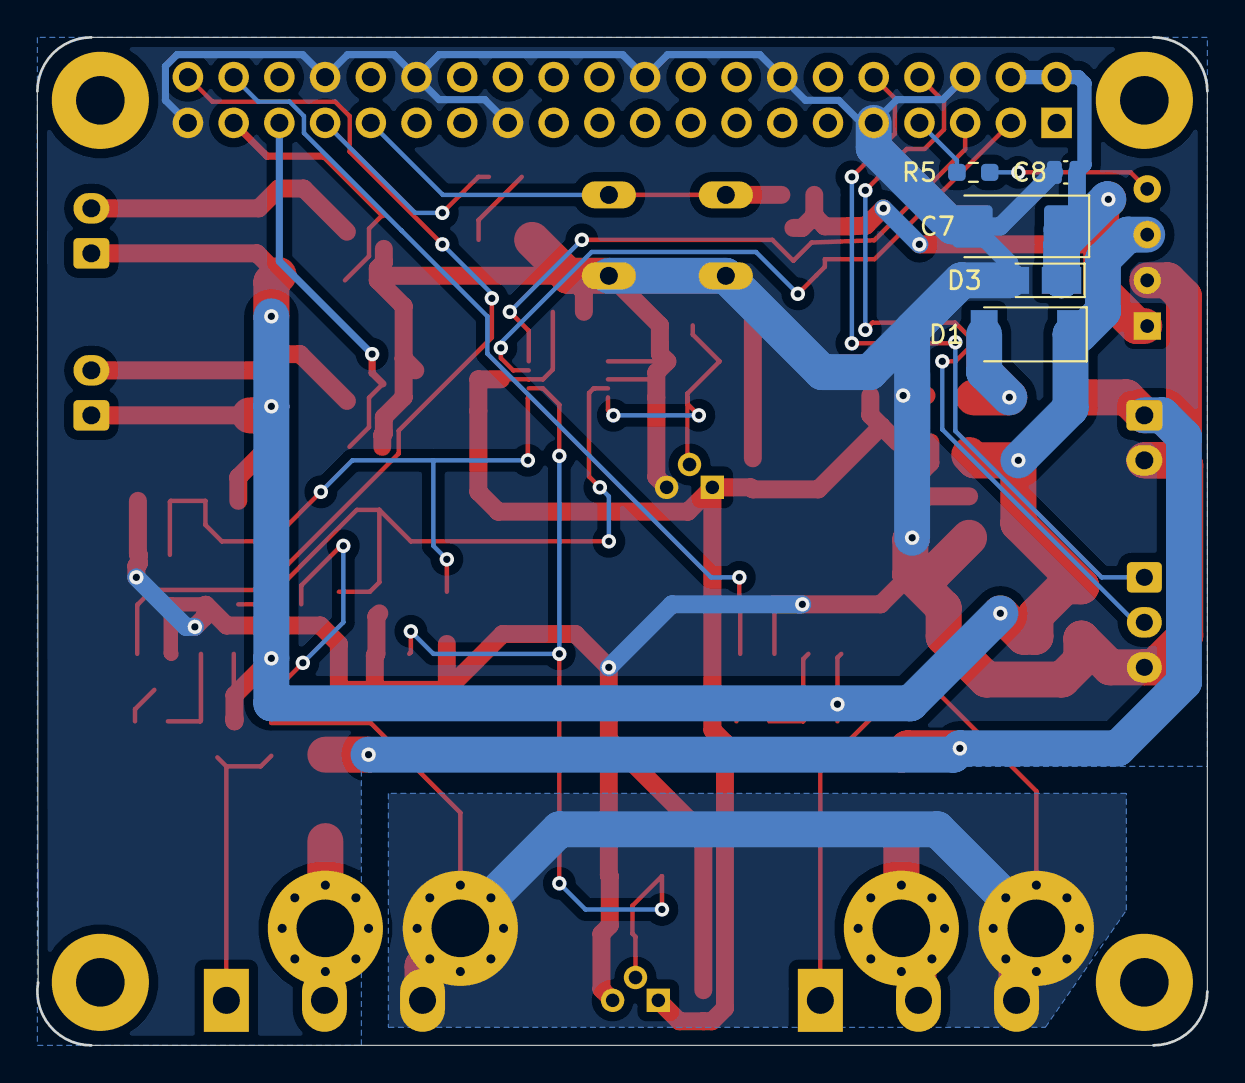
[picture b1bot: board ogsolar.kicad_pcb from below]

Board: 2 copper layers, 65.0 x 56.0 mm, 70 parts (5 on the bottom side), 35 nets.

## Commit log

2021-10-02 Initial commit of RPi ogsolar.
2021-10-02 Add script to deploy files to target machine when testing.
2021-10-05 - Add RPi heasink and CPU temperatures to web interface. - Remove references to Omega2 as this platform is no longer supported.
2021-10-06 - Add the RPi heatsink temp and CPU temp to the web server data. - Auto start a Tornado web server rather than using the external (ws) web server (binds to port 8080).
2021-10-06 Add the web server src file.
2021-10-15 Correct comment.
2021-10-15 Improve the README.
2021-10-15 Simplify the setup.py and include the web server files in the installed module.
2021-10-15 Add a documentation folder.
2021-10-15 Add the files that comprise the web interface.
2021-10-15 Add a document that details how to setup the raspberry PI with the OGSolar PCB attached.
2021-10-16 Managed the web root folder. The web root is created in the temp file system when ogsolar starts from the ogsolar/www/html folder in site-packages.
2021-10-16 Bump to version 4.4
2021-10-16 Remove the deploy script as it's not needed in the release.
2021-10-17 Use the laytest p3lib to ensure that syslog messages include the host IP address.
2021-10-17 Update to disable the syslog server on the RPi.
2021-10-18 Update to detail the commands to turn off the syslog server on the RPi to reduce filesystem writes.
2021-10-18 fix the web server root folder (no longer /www but sits in /tmp) and rationalise the WebServer class to bring all the web server code into it.
2021-10-18 Add an MIT license to the project.
2021-10-18 Add low current threshold to stop -0.0 reported currents in web interface.
2021-10-18 Bump version to 4.5
2021-10-19 Update comment to clarify the web root folder details.
2021-10-20 Add details of how the initial SD card is created.
2021-10-20 Update with details of the previous ogsolar project.
2021-10-20 Add the hardware (schematic, PCB and case designs).
2021-10-21 Update to title and some grammar.
2021-12-30 Add messages to indicate which json files are written for the web server interface.
2022-02-10 Compare the AYT message key value rather than the message string as the exact format of the AYT JSON string may vary.
2022-12-27 Fix setting spare relay output.
2022-12-27 Allow yview client to bind to specific interface. This is useful if we have multiple networks available and we only wish to send back to the YView gateway on one interface.
2022-12-27 Add the ability to use the spare relay output to connect to an AC mains battery charger to charge the battery in the event that there is insufficient solar energy to keep the battery above the minimu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
2022-12-27 Don't charge the battery from mains AC if it's temperature is below 0 °C.
